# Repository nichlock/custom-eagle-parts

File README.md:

# custom-eagle-parts
My parts library for EAGLE.

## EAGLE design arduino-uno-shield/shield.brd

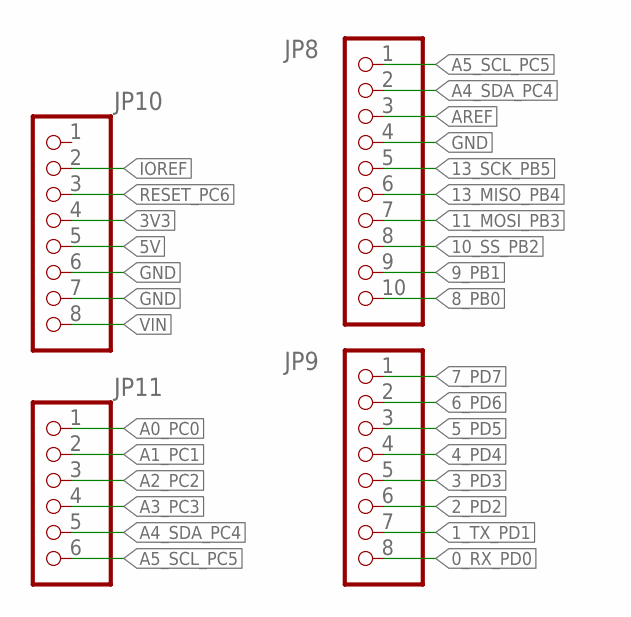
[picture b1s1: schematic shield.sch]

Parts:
JP8: PINHD-1X10; 1X10
JP9, JP10: PINHD-1X8; 1X08
JP11: PINHD-1X6; 1X06

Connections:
0_RX_PD0: JP9.8
1_TX_PD1: JP9.7
2_PD2: JP9.6
3V3: JP10.4
3_PD3: JP9.5
4_PD4: JP9.4
5V: JP10.5
5_PD5: JP9.3
6_PD6: JP9.2
7_PD7: JP9.1
8_PB0: JP8.10
9_PB1: JP8.9
10_SS_PB2: JP8.8
11_MOSI_PB3: JP8.7
13_MISO_PB4: JP8.6
13_SCK_PB5: JP8.5
A0_PC0: JP11.1
A1_PC1: JP11.2
A2_PC2: JP11.3
A3_PC3: JP11.4
A4_SDA_PC4: JP8.2, JP11.5
A5_SCL_PC5: JP8.1, JP11.6
AREF: JP8.3
GND: JP8.4, JP10.6, JP10.7
IOREF: JP10.2
RESET_PC6: JP10.3
VIN: JP10.8

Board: 2 copper layers, 4 parts (0 on the bottom side), 3 nets, no tracks yet.

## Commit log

2020-08-25 Initial file commit
2020-09-01 Fix tCream for VDFN-8
2021-03-16 Add some libraries
2022-01-11 reworked files and added ULPs
2022-05-11 Add Arduino shield base files
2022-05-11 Add AD8515
